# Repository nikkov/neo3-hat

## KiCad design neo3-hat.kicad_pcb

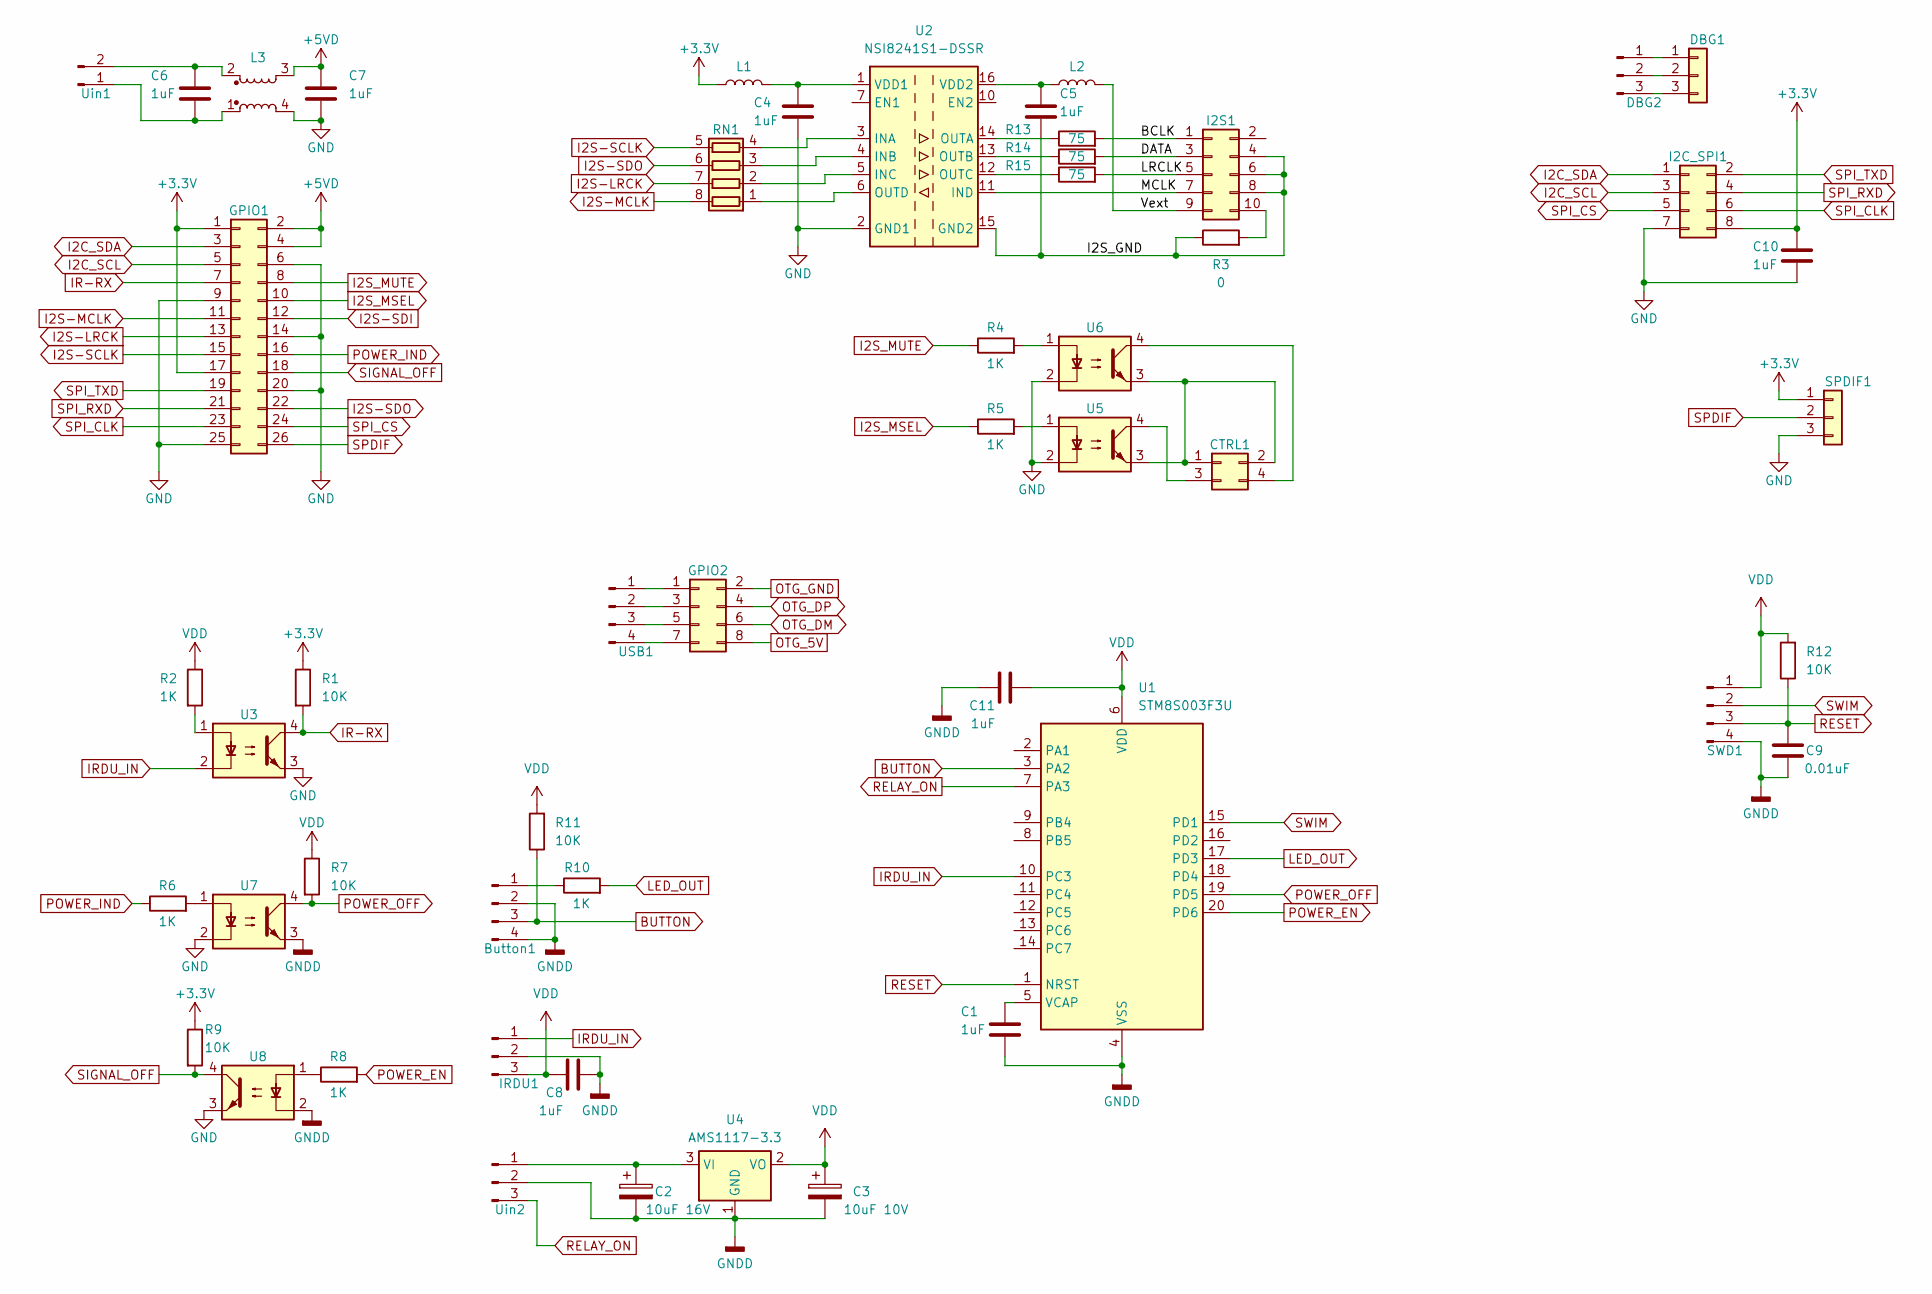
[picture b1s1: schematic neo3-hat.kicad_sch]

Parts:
Button1: Conn_01x04_Pin; JST_GH_1x04_P1.25mm_Horizontal
C1, C11: 1uF; C_0402_1005Metric
C2: 10uF 16V; CP_Radial_D5.0mm_P2.00mm
C3: 10uF 10V; CP_Radial_D5.0mm_P2.00mm
C4, C5, C8, C10: 1uF; C_0603_1608Metric
C6, C7: 1uF; C_0805_2012Metric
C9: 0.01uF; C_0402_1005Metric
CTRL1: Conn_02x02_Odd_Even; PinHeader_2x02_P2.54mm_Vertical
DBG1: Conn_01x03; PinSocket_1x03_P2.54mm_Vertical
DBG2: Conn_01x03_Pin; JST_PH_B3B-PH-K_1x03_P2.00mm_Vertical
GPIO1: Conn_02x13_Odd_Even; PinSocket_2x13_P2.54mm_Vertical
GPIO2: Conn_02x04_Odd_Even; PinSocket_2x04_P2.54mm_Vertical
I2C_SPI1: Conn_02x04_Odd_Even; JST_PHD_B8B-PHDSS_2x04_P2.00mm_Vertical
I2S1: Conn_02x05_Odd_Even; PinHeader_2x05_P2.54mm_Vertical
IRDU1: Conn_01x03_Pin; JST_GH_1x03_P1.25mm_Horizontal
L1, L2: BLM0603; L_0603_1608Metric
L3: CPFC74
R1, R7, R9, R11, R12: 10K; R_0402_1005Metric
R2, R4, R5, R6, R8, R10: 1K; R_0402_1005Metric
R3: 0; R_0402_1005Metric
R13, R14, R15: 75; R_0402_1005Metric
RN1: R_Pack04; R_Array_Convex_4x0603
SPDIF1: Conn_01x03; JST_PH_B3B-PH-K_1x03_P2.00mm_Vertical
SWD1: Conn_01x04_Pin; JST_GH_1x04_P1.25mm_Vertical
U1: STM8S003F3U; ST_UFQFPN-20_3x3mm_P0.5mm
U2: NSI8241S1-DSSR; SSOP-16_3.9x4.9mm_P0.635mm
U3, U5, U6, U7, U8: PS2801-1; SO-4_4.4x2.3mm_P1.27mm
U4: AMS1117-3.3; SOT-223-3_TabPin2
USB1: Conn_01x04_Pin; JST_PH_B4B-PH-K_1x04_P2.00mm_Vertical
Uin1: Conn_01x02_Pin; JST_EH_S2B-EH_1x02_P2.50mm_Horizontal
Uin2: Conn_01x03_Pin; JST_GH_1x03_P1.25mm_Horizontal

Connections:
+3.3V: C10.1, GPIO1.1, GPIO1.17, I2C_SPI1.8, L1.1, R1.1, R9.1, SPDIF1.1
+5VD: C7.2, GPIO1.2, GPIO1.4, L3.3
/BCLK: I2S1.1, R13.2
/DATA: I2S1.3, R14.2
/I2S_GND: C5.2, I2S1.4, I2S1.6, I2S1.8, R3.1, U2.9 (GND2), U2.15 (GND2)
/LRCLK: I2S1.5, R15.2
/MCLK: I2S1.7, U2.11 (IND)
/Vext: I2S1.9, L2.2
BUTTON: Button1.3, R11.1, U1.3 (PA2)
GND: C4.2, C7.1, C10.2, GPIO1.6, GPIO1.9, GPIO1.14, GPIO1.20, GPIO1.25, I2C_SPI1.7, L3.4, SPDIF1.3, U2.2 (GND1), U2.8 (GND1), U3.3, U5.2, U6.2, U7.2, U8.3
GNDD: Button1.2, Button1.4, C1.2, C2.2, C3.2, C8.2, C9.1, C11.1, IRDU1.2, SWD1.4, U1.4 (VSS), U4.1 (GND), U7.3, U8.2, Uin2.2
I2C_SCL: GPIO1.5, I2C_SPI1.3
I2C_SDA: GPIO1.3, I2C_SPI1.1
I2S-LRCK: GPIO1.13, RN1.7 (R2.2)
I2S-MCLK: GPIO1.11, RN1.8 (R1.2)
I2S-SCLK: GPIO1.15, RN1.5 (R4.2)
I2S-SDI: GPIO1.12
I2S-SDO: GPIO1.22, RN1.6 (R3.2)
I2S_MSEL: GPIO1.10, R5.1
I2S_MUTE: GPIO1.8, R4.1
IR-RX: GPIO1.7, R1.2, U3.4
IRDU_IN: IRDU1.1, U1.10 (PC3), U3.2
LED_OUT: R10.2, U1.17 (PD3)
unnamed: Button1.1, R10.1
unnamed: CTRL1.1, CTRL1.2, U5.3, U6.3
unnamed: CTRL1.3, U5.4
unnamed: CTRL1.4, U6.4
unnamed: DBG1.1, DBG2.1
unnamed: DBG1.2, DBG2.2
unnamed: DBG1.3, DBG2.3
unnamed: GPIO2.1, USB1.1
unnamed: GPIO2.3, USB1.2
unnamed: GPIO2.5, USB1.3
unnamed: GPIO2.7, USB1.4
unnamed: I2S1.10, R3.2
unnamed: R2.2, U3.1
unnamed: R4.2, U6.1
unnamed: R5.2, U5.1
unnamed: R6.2, U7.1
unnamed: R8.1, U8.1
unnamed: RN1.1 (R1.1), U2.6 (OUTD)
unnamed: RN1.2 (R2.1), U2.5 (INC)
unnamed: RN1.3 (R3.1), U2.4 (INB)
unnamed: RN1.4 (R4.1), U2.3 (INA)
unnamed: C1.1, U1.5 (VCAP)
unnamed: R13.1, U2.14 (OUTA)
unnamed: R14.1, U2.13 (OUTB)
unnamed: R15.1, U2.12 (OUTC)
unnamed: C4.1, L1.2, U2.1 (VDD1)
unnamed: C5.1, L2.1, U2.16 (VDD2)
unnamed: C2.1, U4.3 (VI), Uin2.1
unnamed: C6.1, L3.1, Uin1.1
unnamed: C6.2, L3.2, Uin1.2
OTG_5V: GPIO2.8
OTG_DM: GPIO2.6
OTG_DP: GPIO2.4
OTG_GND: GPIO2.2
POWER_EN: R8.2, U1.20 (PD6)
POWER_IND: GPIO1.16, R6.1
POWER_OFF: R7.2, U1.19 (PD5), U7.4
RELAY_ON: U1.7 (PA3), Uin2.3
RESET: C9.2, R12.1, SWD1.3, U1.1 (NRST)
SIGNAL_OFF: GPIO1.18, R9.2, U8.4
SPDIF: GPIO1.26, SPDIF1.2
SPI_CLK: GPIO1.23, I2C_SPI1.6
SPI_CS: GPIO1.24, I2C_SPI1.5
SPI_RXD: GPIO1.21, I2C_SPI1.4
SPI_TXD: GPIO1.19, I2C_SPI1.2
SWIM: SWD1.2, U1.15 (PD1)
VDD: C3.1, C8.1, C11.2, IRDU1.3, R2.1, R7.1, R11.2, R12.2, SWD1.1, U1.6 (VDD), U4.2 (VO)

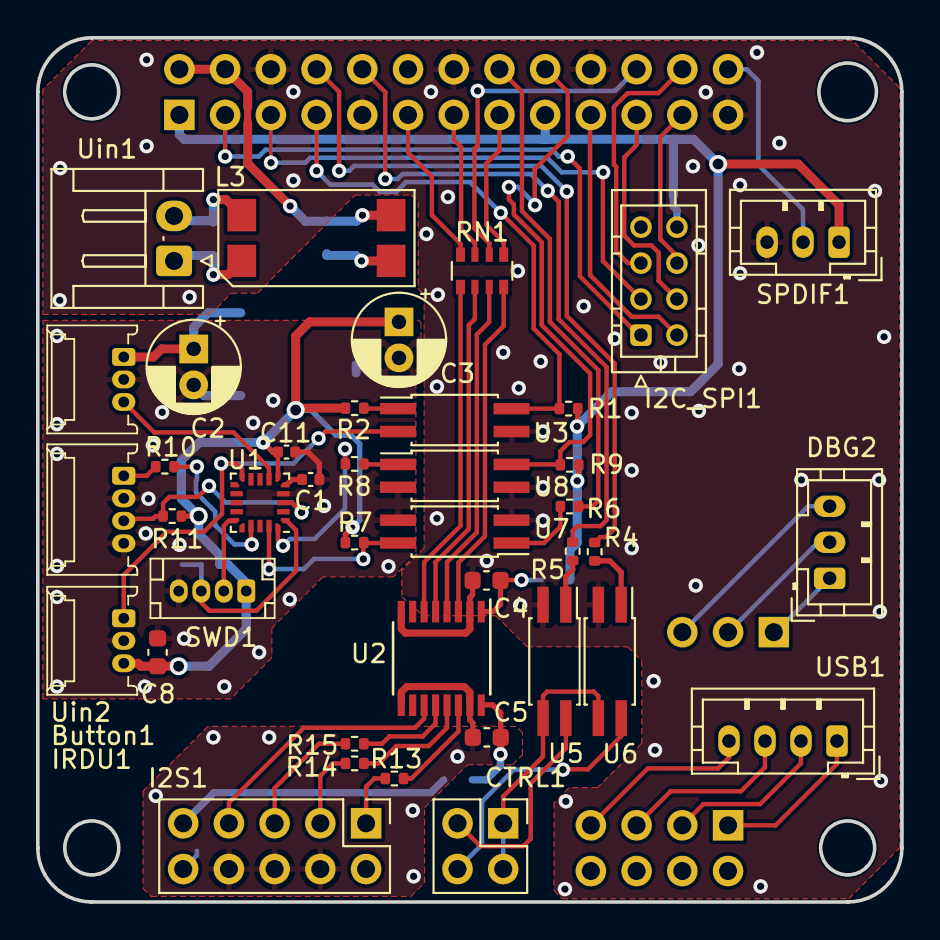
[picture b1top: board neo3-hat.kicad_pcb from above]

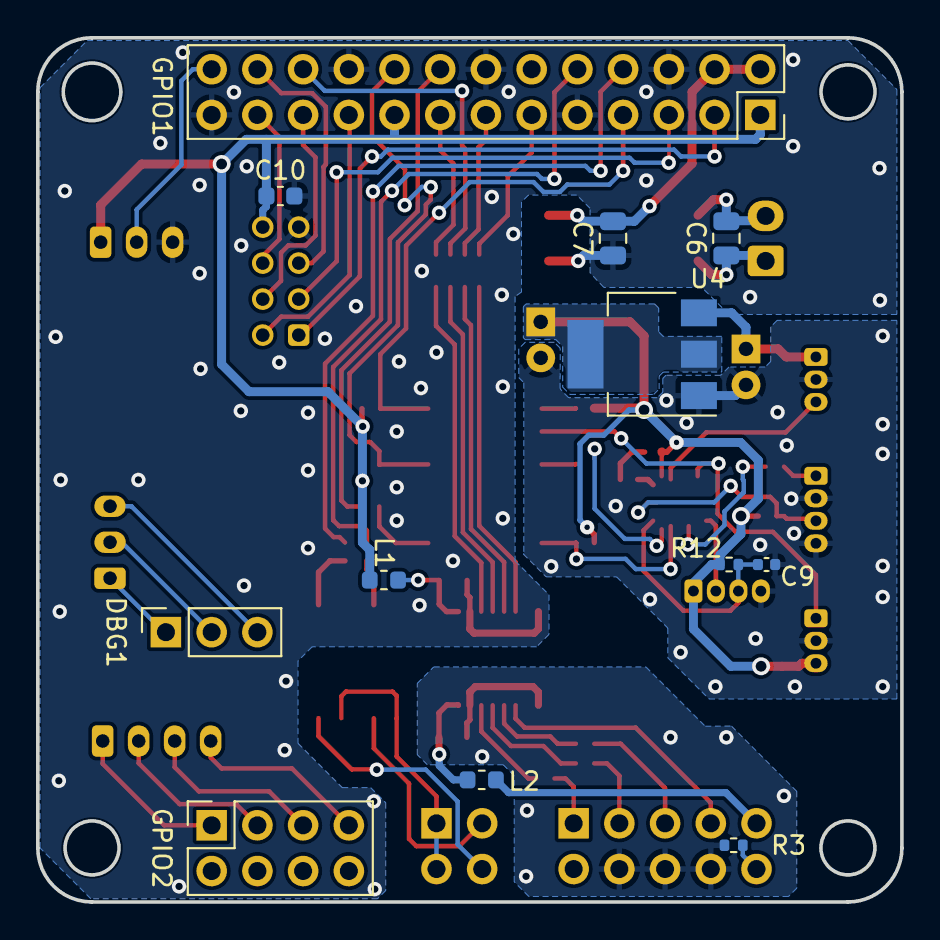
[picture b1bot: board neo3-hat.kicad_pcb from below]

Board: 2 copper layers, 48.0 x 48.0 mm, 52 parts (12 on the bottom side), 65 nets.
